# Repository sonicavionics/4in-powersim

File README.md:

# Power Sim Module Repository

---

<div align="center">
  <div>

    <p><em>3D Render</em></p>
  </div>
  <br>

  <div>
    <br>
    <p><em>Schematic</em></p>
  </div>
  <br>
  
  <div>
    
    <br>
    <em>Footprint</em>
  </div>
</div>

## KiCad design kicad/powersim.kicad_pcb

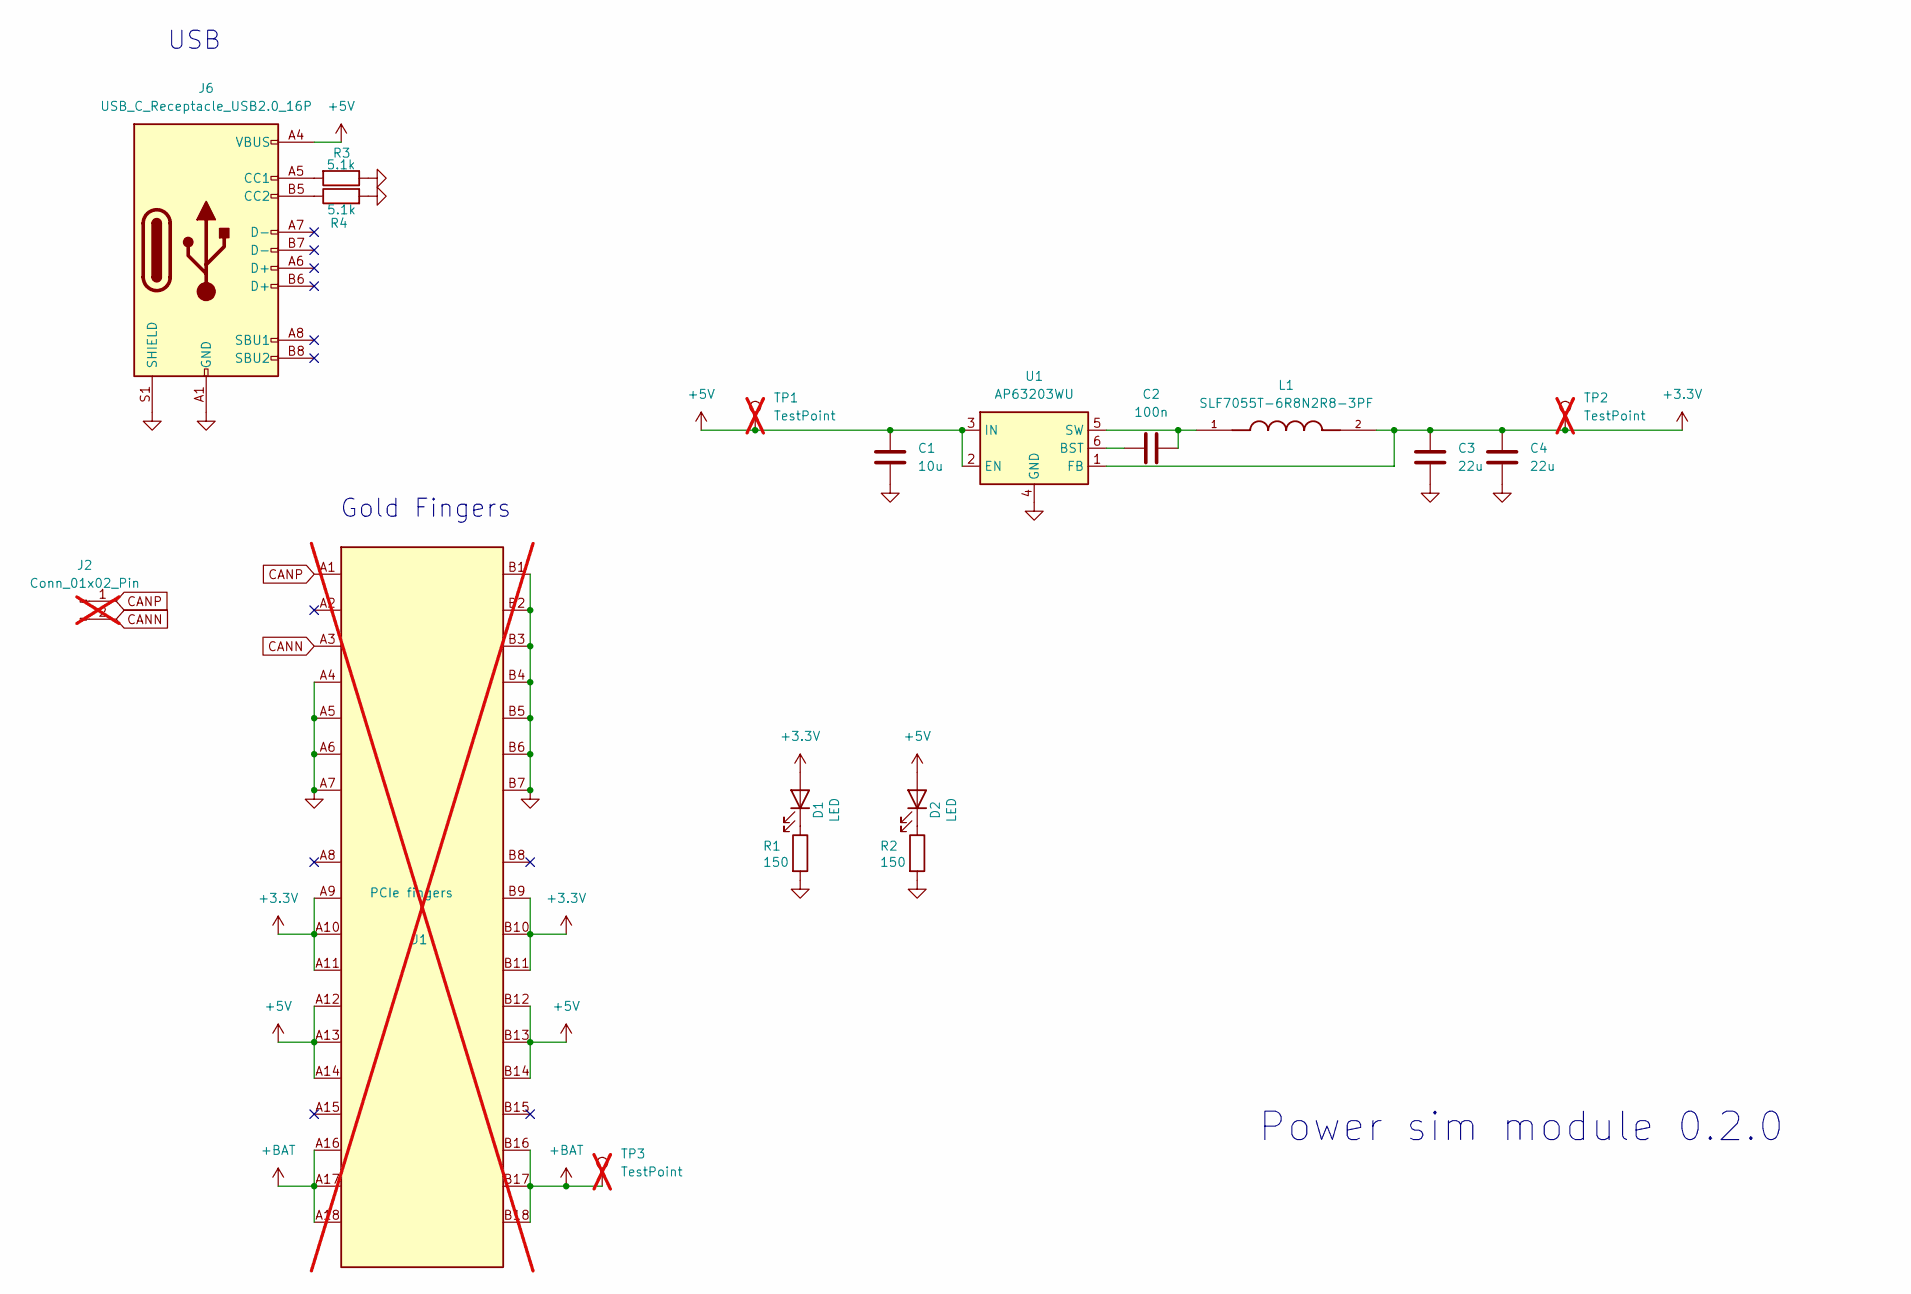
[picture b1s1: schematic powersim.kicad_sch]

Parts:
C1: 10u; C_0402_1005Metric; LCSC Part # C15525
C2: 100n; C_0402_1005Metric; LCSC Part # C307331
C3, C4: 22u; C_0603_1608Metric; LCSC Part # C59461
D1, D2: LED; LED_0603_1608Metric; LCSC Part # C2286
J1: Bus_PCI_Express_x1; BUS_PCIexpress_x1; LCSC Part # n/a; not fitted
J2: Conn_01x02_Pin; PinHeader_1x02_P2.54mm_Vertical; not fitted
J6: USB_C_Receptacle_USB2.0_16P; USB_C_Receptacle_Palconn_UTC16-G; LCSC Part # C2765186
L1: SLF7055T-6R8N2R8-3PF; IND_SLF7055T-6R8N2R8-3PF; PARTREV N/A; LCSC Part # C21218
R1, R2: 150; R_0603_1608Metric; LCSC Part # C22808
R3, R4: 5.1k; R_0402_1005Metric; LCSC Part # C25905
TP1, TP2, TP3: TestPoint; PinHeader_1x01_P2.54mm_Vertical; not fitted
U1: AP63203WU; TSOT-23-6; LCSC Part # C780769

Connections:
+3.3V: C3.1, C4.1, D1.2 (A), J1.A9 (+3.3V), J1.A10 (+3.3V), J1.A11 (~PERST), J1.B9 (JTAG1), J1.B10 (3.3Vaux), J1.B11 (~WAKE), L1.2, TP2.1, U1.1 (FB)
+5V: C1.1, D2.2 (A), J1.A12 (GND), J1.A13 (REFCLK+), J1.A14 (REFCLK-), J1.B12 (RSVD), J1.B13 (GND), J1.B14 (PETp0), J6.A4 (VBUS), J6.A9 (VBUS), J6.B4 (VBUS), J6.B9 (VBUS), TP1.1, U1.2 (EN), U1.3 (IN)
+BAT: J1.A16 (PERp0), J1.A17 (PERn0), J1.A18 (GND), J1.B16 (GND), J1.B17 (~PRSNT2), J1.B18 (GND), TP3.1
CANN: J1.A3 (+12V), J2.2
CANP: J1.A1 (~PRSNT1), J2.1
GND: C1.2, C3.2, C4.2, J1.A4 (GND), J1.A5 (JTAG2), J1.A6 (JTAG3), J1.A7 (JTAG4), J1.B1 (+12V), J1.B2 (+12V), J1.B3 (+12V), J1.B4 (GND), J1.B5 (SMCLK), J1.B6 (SMDAT), J1.B7 (GND), J6.A1 (GND), J6.A12 (GND), J6.B1 (GND), J6.B12 (GND), J6.S1 (SHIELD), R1.2, R2.2, R3.1, R4.2, U1.4 (GND)
unnamed: D1.1 (K), R1.1
unnamed: D2.1 (K), R2.1
unnamed: J6.A5 (CC1), R3.2
unnamed: J6.B5 (CC2), R4.1
unnamed: C2.1, U1.6 (BST)
unnamed: C2.2, L1.1, U1.5 (SW)

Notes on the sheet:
USB
Power sim module 0.2.0
Gold Fingers

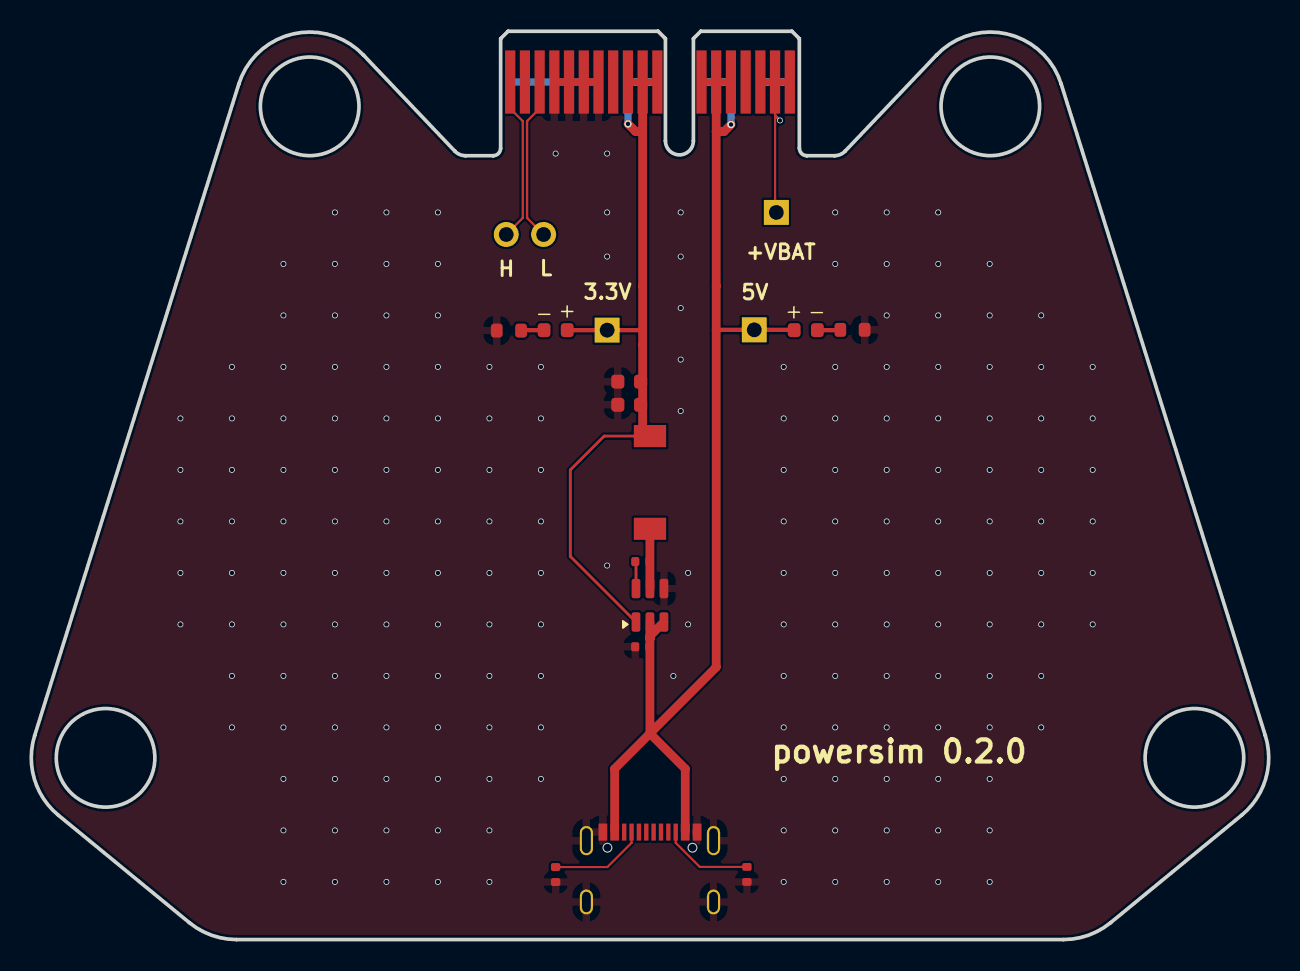
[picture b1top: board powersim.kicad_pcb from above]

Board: 2 copper layers, 84.1 x 61.7 mm, 18 parts (1 on the bottom side), 12 nets.

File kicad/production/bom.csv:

Designator,Footprint,Quantity,Value,LCSC Part #
C1,0402,1,10u,C15525
C2,0402,1,100n,C307331
"C3, C4",0603,2,22u,C59461
"D1, D2",0603,2,LED,C2286
J6,USB_C_Receptacle_Palconn_UTC16-G,1,USB_C_Receptacle_USB2.0_16P,C2765186
L1,IND_SLF7055T-6R8N2R8-3PF,1,SLF7055T-6R8N2R8-3PF,C21218
"R1, R2",0603,2,150,C22808
"R3, R4",0402,2,5.1k,C25905
U1,TSOT-23-6,1,AP63203WU,C780769

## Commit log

2025-01-05 init
2025-01-05 Update .gitignore to include additional backup directory patterns
2025-01-07 init github action
2025-01-07 Auto-exported schematic, PCB, and 3D model
2025-01-07 Create use-export-kicad
2025-01-07 Rename use-export-kicad to use-export-kicad.yml
2025-01-08 add library to kicad folder
2025-01-15 add test points and USB pull down resistors
2025-01-16 update board outline, delete old production files
2025-01-17 finalize board, update production files
2025-02-05 Update images
